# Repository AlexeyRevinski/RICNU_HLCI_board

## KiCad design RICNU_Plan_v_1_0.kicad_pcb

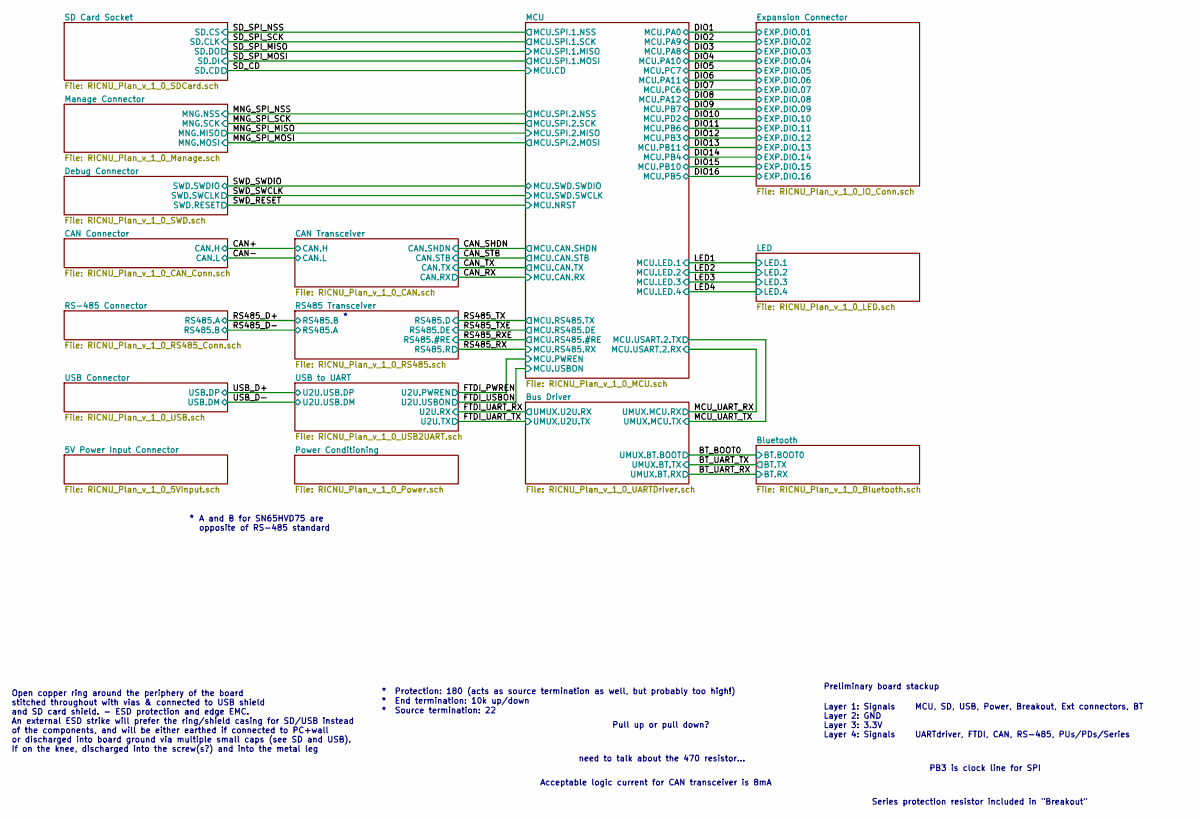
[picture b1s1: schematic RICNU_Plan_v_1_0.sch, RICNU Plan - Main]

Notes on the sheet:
Pull up or pull down?
* Protection: 180 (acts as source termination as well, but probably too high!)
* End termination: 10k up/down
* Source termination: 22
Acceptable logic current for CAN transceiver is 8mA
Series protection resistor included in "Breakout"
need to talk about the 470 resistor...
Open copper ring around the periphery of the board stitched throughout with vias & connected to USB shield and SD card shield. - ESD protection and edge EMC. An external ESD strike will prefer the ring/shield casing for SD/USB instead of the components, and will be either earthed if connected to PC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
PB3 is clock line for SPI
Layer 1: Signals Layer 2: GND Layer 3: 3.3V Layer 4: Signals
MCU, SD, USB, Power, Breakout, Ext connectors, BT UARTdriver, FTDI, CAN, RS-485, PUs/PDs/Series
Preliminary board stackup
A and B for SN65HVD75 are opposite of RS-485 standard

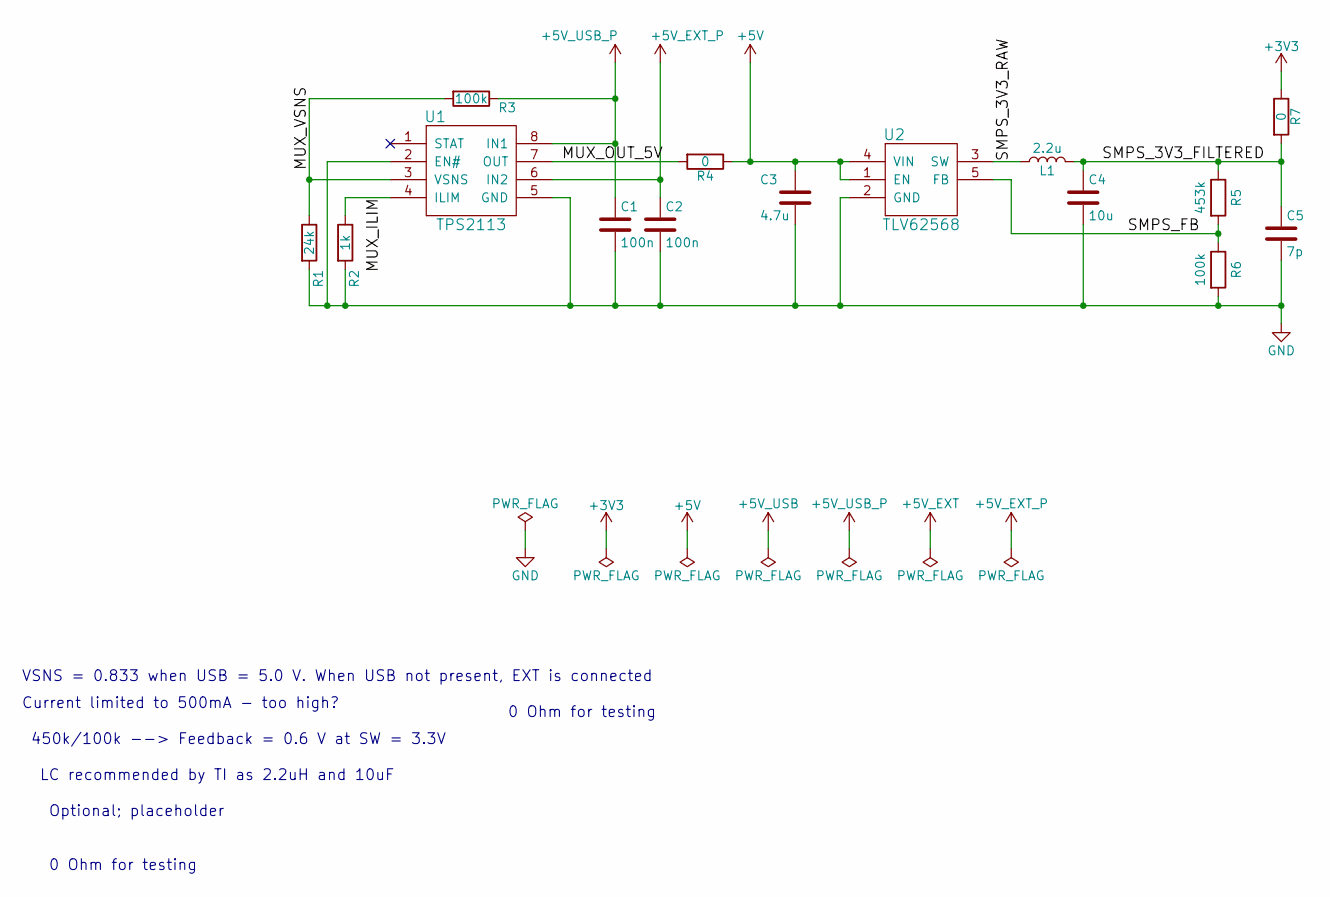
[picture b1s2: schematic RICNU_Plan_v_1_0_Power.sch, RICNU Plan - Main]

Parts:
C1, C2: 100n; C_0402_NoSilk
C3: 4.7u; C_0805
C4: 10u; C_0805
C5: 7p; C_0402_NoSilk
L1: 2.2u; L_Taiyo-Yuden_NR-50xx_HandSoldering
R1: 24k; R_0402_NoSilk
R2: 1k; R_0402_NoSilk
R3, R6: 100k; R_0402_NoSilk
R4, R7: 0; R_0402_NoSilk
R5: 453k; R_0402_NoSilk
U1: TPS2113; TSSOP-8_4.4x3mm_Pitch0.65mm
U2: TLV62568; SOT-23-5

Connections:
+3V3: R7.1; also elsewhere on the board
+5V: C3.1, R4.1, U2.1 (EN), U2.4 (VIN)
+5V_EXT_P: C2.1, U1.6 (IN2); also elsewhere on the board
+5V_USB_P: C1.1, R3.1, U1.8 (IN1); also elsewhere on the board
/Power Conditioning/MUX_ILIM: R2.1, U1.4 (ILIM)
/Power Conditioning/MUX_OUT_5V: R4.2, U1.7 (OUT)
/Power Conditioning/MUX_VSNS: R1.1, R3.2, U1.3 (VSNS)
/Power Conditioning/SMPS_3V3_FILTERED: C4.1, C5.1, L1.2, R5.1, R7.2
/Power Conditioning/SMPS_3V3_RAW: L1.1, U2.3 (SW)
/Power Conditioning/SMPS_FB: R5.2, R6.1, U2.5 (FB)
GND: C1.2, C2.2, C3.2, C4.2, C5.2, R1.2, R2.2, R6.2, U1.2 (EN#), U1.5 (GND), U2.2 (GND); also elsewhere on the board

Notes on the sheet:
0 Ohm for testing
450k/100k --> Feedback = 0.6 V at SW = 3.3V
LC recommended by TI as 2.2uH and 10uF
Optional; placeholder
VSNS = 0.833 when USB = 5.0 V. When USB not present, EXT is connected
Current limited to 500mA - too high?

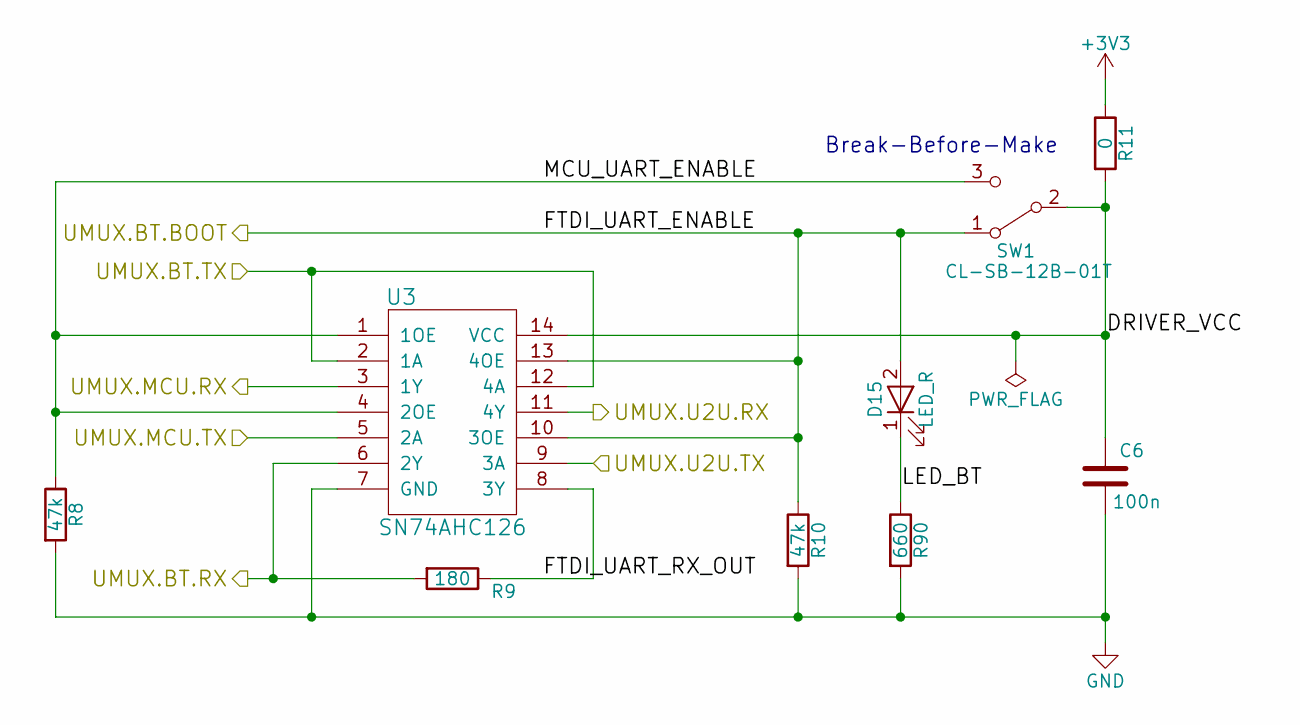
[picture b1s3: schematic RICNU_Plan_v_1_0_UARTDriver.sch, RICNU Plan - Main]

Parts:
C6: 100n; C_0402_NoSilk
D15: LED_R; LED_0402
R8, R10: 47k; R_0402_NoSilk
R9: 180; R_0402_NoSilk
R11: 0; R_0402_NoSilk
R90: 660; R_0402_NoSilk
SW1: CL-SB-12B-01T
U3: SN74AHC126; TSSOP-14_4.4x5mm_Pitch0.65mm

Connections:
+3V3: R11.1; also elsewhere on the board
/BT_BOOT0: D15.2 (A), R10.1, SW1.1 (A), U3.10 (3OE), U3.13 (4OE); also elsewhere on the board
/BT_UART_RX: R9.2, U3.6 (2Y); also elsewhere on the board
/BT_UART_TX: U3.2 (1A), U3.12 (4A); also elsewhere on the board
/Bus Driver/DRIVER_VCC: C6.1, R11.2, SW1.2 (B), U3.14 (VCC)
/Bus Driver/FTDI_UART_RX_OUT: R9.1, U3.8 (3Y)
/Bus Driver/LED_BT: D15.1 (K), R90.1
/Bus Driver/MCU_UART_ENABLE: R8.1, SW1.3 (C), U3.1 (1OE), U3.4 (2OE)
/FTDI_UART_RX: U3.11 (4Y); also elsewhere on the board
/FTDI_UART_TX: U3.9 (3A); also elsewhere on the board
/MCU_UART_RX: U3.3 (1Y); also elsewhere on the board
/MCU_UART_TX: U3.5 (2A); also elsewhere on the board
GND: C6.2, R8.2, R10.2, R90.2, U3.7 (GND); also elsewhere on the board

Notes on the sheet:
Break-Before-Make

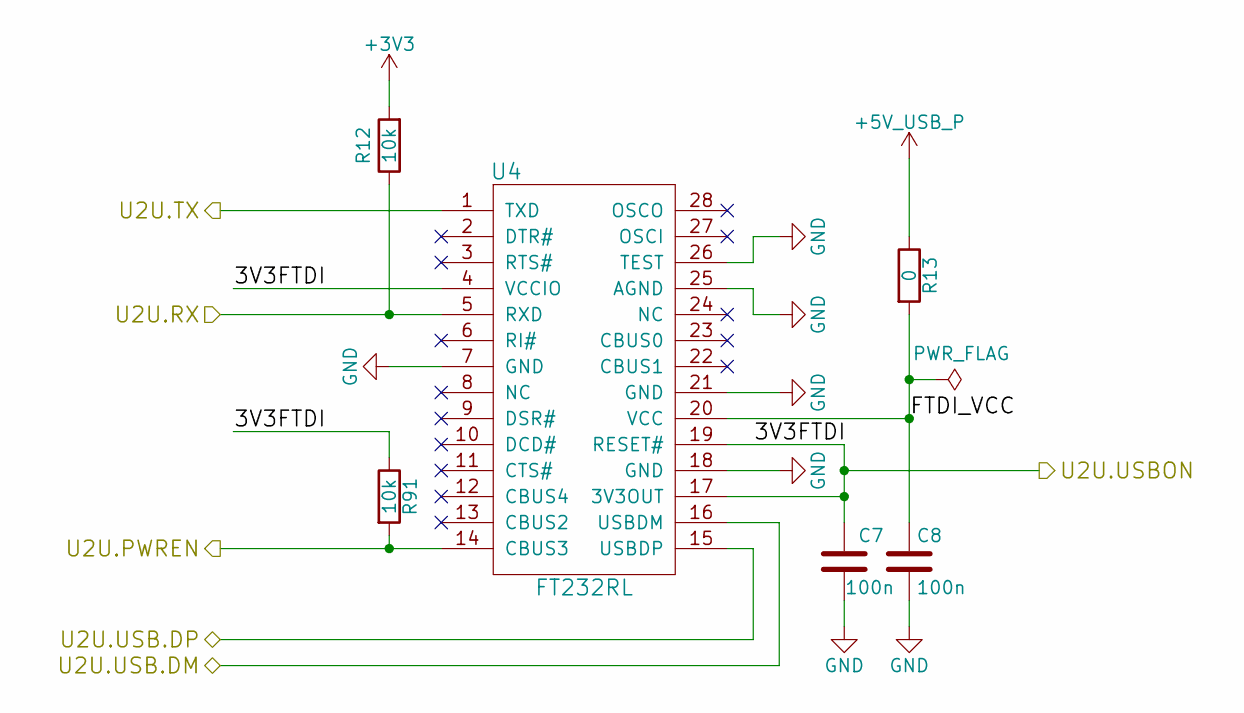
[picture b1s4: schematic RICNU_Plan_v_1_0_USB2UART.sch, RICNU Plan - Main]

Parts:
C7, C8: 100n; C_0402_NoSilk
R12, R91: 10k; R_0402_NoSilk
R13: 0; R_0402_NoSilk
U4: FT232RL; SSOP-28_5.3x10.2mm_Pitch0.65mm

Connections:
+3V3: R12.2; also elsewhere on the board
+5V_USB_P: R13.1; also elsewhere on the board
/FTDI_PWREN: R91.2, U4.14 (CBUS3); also elsewhere on the board
/FTDI_UART_RX: R12.1, U4.5 (RXD); also elsewhere on the board
/FTDI_UART_TX: U4.1 (TXD); also elsewhere on the board
/FTDI_USBON: C7.1, R91.1, U4.4 (VCCIO), U4.17 (3V3OUT), U4.19 (RESET#); also elsewhere on the board
/USB to UART/FTDI_VCC: C8.1, R13.2, U4.20 (VCC)
/USB_D+: U4.15 (USBDP); also elsewhere on the board
/USB_D-: U4.16 (USBDM); also elsewhere on the board
GND: C7.2, C8.2, U4.7 (GND), U4.18 (GND), U4.21 (GND), U4.25 (AGND), U4.26 (TEST); also elsewhere on the board

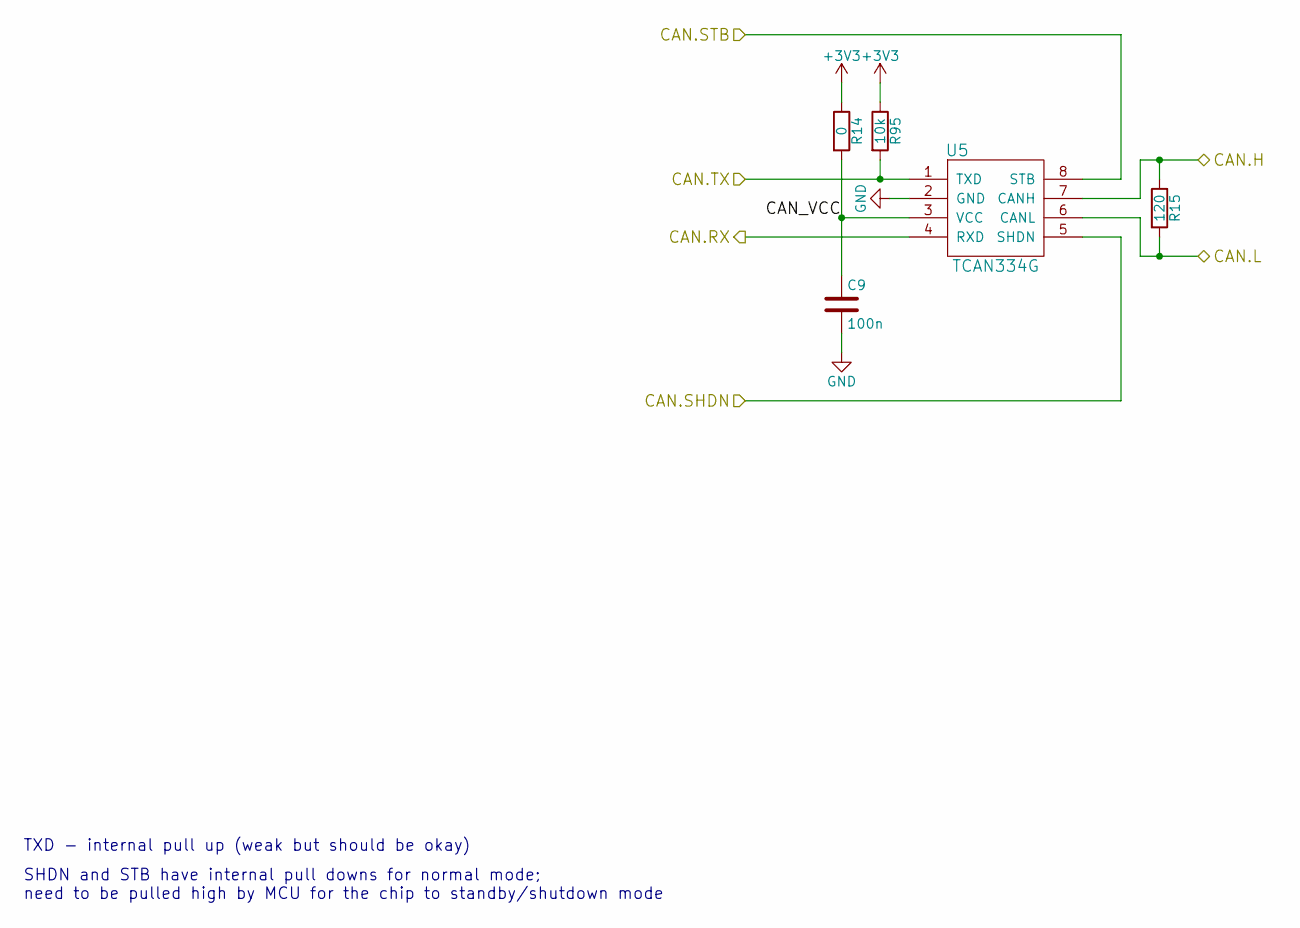
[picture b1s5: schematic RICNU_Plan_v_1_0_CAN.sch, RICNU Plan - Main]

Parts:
C9: 100n; C_0402_NoSilk
R14: 0; R_0402_NoSilk
R15: 120; R_0402_NoSilk
R95: 10k; R_0402_NoSilk
U5: TCAN334G; SOT-23-8

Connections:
+3V3: R14.1, R95.1; also elsewhere on the board
/CAN Transceiver/CAN_VCC: C9.1, R14.2, U5.3 (VCC)
/CAN+: R15.1, U5.7 (CANH); also elsewhere on the board
/CAN-: R15.2, U5.6 (CANL); also elsewhere on the board
/CAN_RX: U5.4 (RXD); also elsewhere on the board
/CAN_SHDN: U5.5 (SHDN); also elsewhere on the board
/CAN_STB: U5.8 (STB); also elsewhere on the board
/CAN_TX: R95.2, U5.1 (TXD); also elsewhere on the board
GND: C9.2, U5.2 (GND); also elsewhere on the board

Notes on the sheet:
SHDN and STB have internal pull downs for normal mode; need to be pulled high by MCU for the chip to standby/shutdown mode
TXD - internal pull up (weak but should be okay)

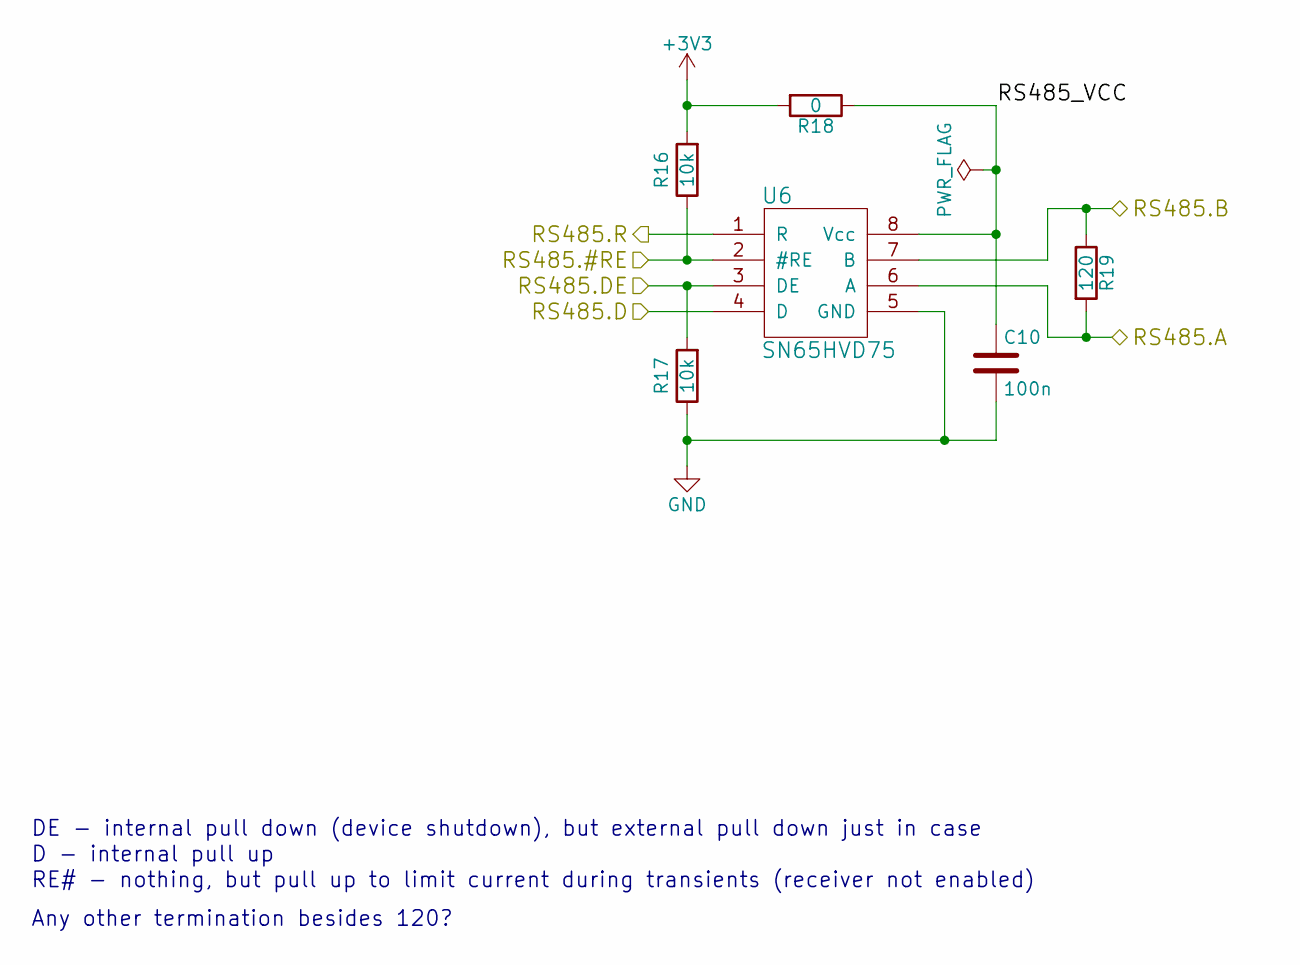
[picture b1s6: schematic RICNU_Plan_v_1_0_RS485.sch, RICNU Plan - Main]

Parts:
C10: 100n; C_0402_NoSilk
R16, R17: 10k; R_0402_NoSilk
R18: 0; R_0402_NoSilk
R19: 120; R_0402_NoSilk
U6: SN65HVD75; VSSOP-8_3.0x3.0mm_Pitch0.65mm

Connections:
+3V3: R16.2, R18.2; also elsewhere on the board
/RS485 Transceiver/RS485_VCC: C10.1, R18.1, U6.8 (Vcc)
/RS485_D+: R19.1, U6.7 (B); also elsewhere on the board
/RS485_D-: R19.2, U6.6 (A); also elsewhere on the board
/RS485_RX: U6.1 (R); also elsewhere on the board
/RS485_RXE: R16.1, U6.2 (#RE); also elsewhere on the board
/RS485_TX: U6.4 (D); also elsewhere on the board
/RS485_TXE: R17.2, U6.3 (DE); also elsewhere on the board
GND: C10.2, R17.1, U6.5 (GND); also elsewhere on the board

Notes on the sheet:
DE - internal pull down (device shutdown), but external pull down just in case
D - internal pull up
RE# - nothing, but pull up to limit current during transients (receiver not enabled)
Any other termination besides 120?

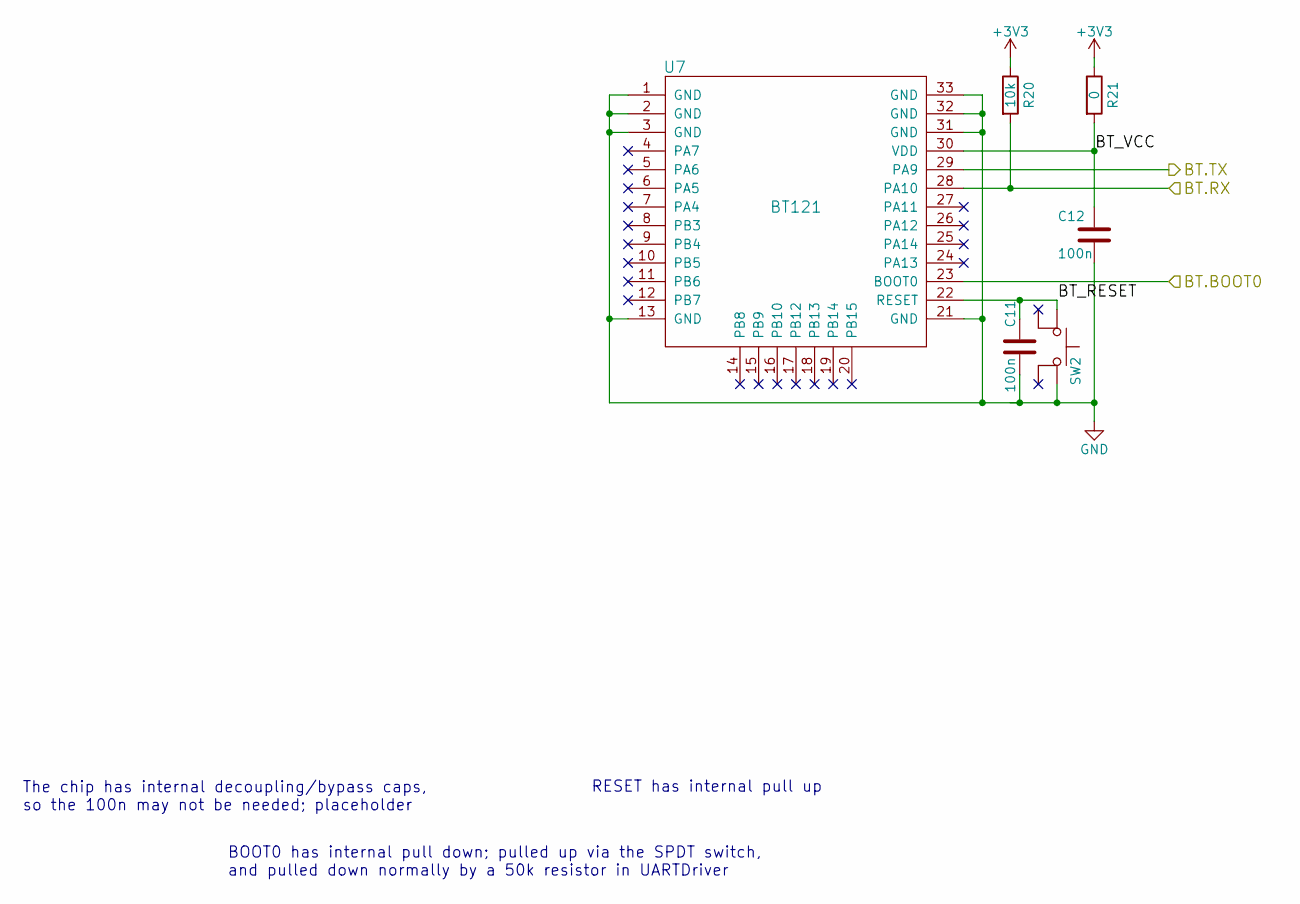
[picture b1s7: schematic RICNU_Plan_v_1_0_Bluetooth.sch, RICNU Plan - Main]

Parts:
C11, C12: 100n; C_0402_NoSilk
R20: 10k; R_0402_NoSilk
R21: 0; R_0402_NoSilk
SW2: SW_Push_4pin; SW_SPST_KMR7
U7: BT121; BT121-A

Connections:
+3V3: R20.1, R21.1; also elsewhere on the board
/BT_BOOT0: U7.23 (BOOT0); also elsewhere on the board
/BT_UART_RX: R20.2, U7.28 (PA10); also elsewhere on the board
/BT_UART_TX: U7.29 (PA9); also elsewhere on the board
/Bluetooth/BT_RESET: C11.1, SW2.1, U7.22 (RESET)
/Bluetooth/BT_VCC: C12.1, R21.2, U7.30 (VDD)
GND: C11.2, C12.2, SW2.2, U7.1 (GND), U7.2 (GND), U7.3 (GND), U7.13 (GND), U7.21 (GND), U7.31 (GND), U7.32 (GND), U7.33 (GND); also elsewhere on the board

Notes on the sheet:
BOOT0 has internal pull down; pulled up via the SPDT switch, and pulled down normally by a 50k resistor in UARTDriver
RESET has internal pull up
The chip has internal decoupling/bypass caps, so the 100n may not be needed; placeholder

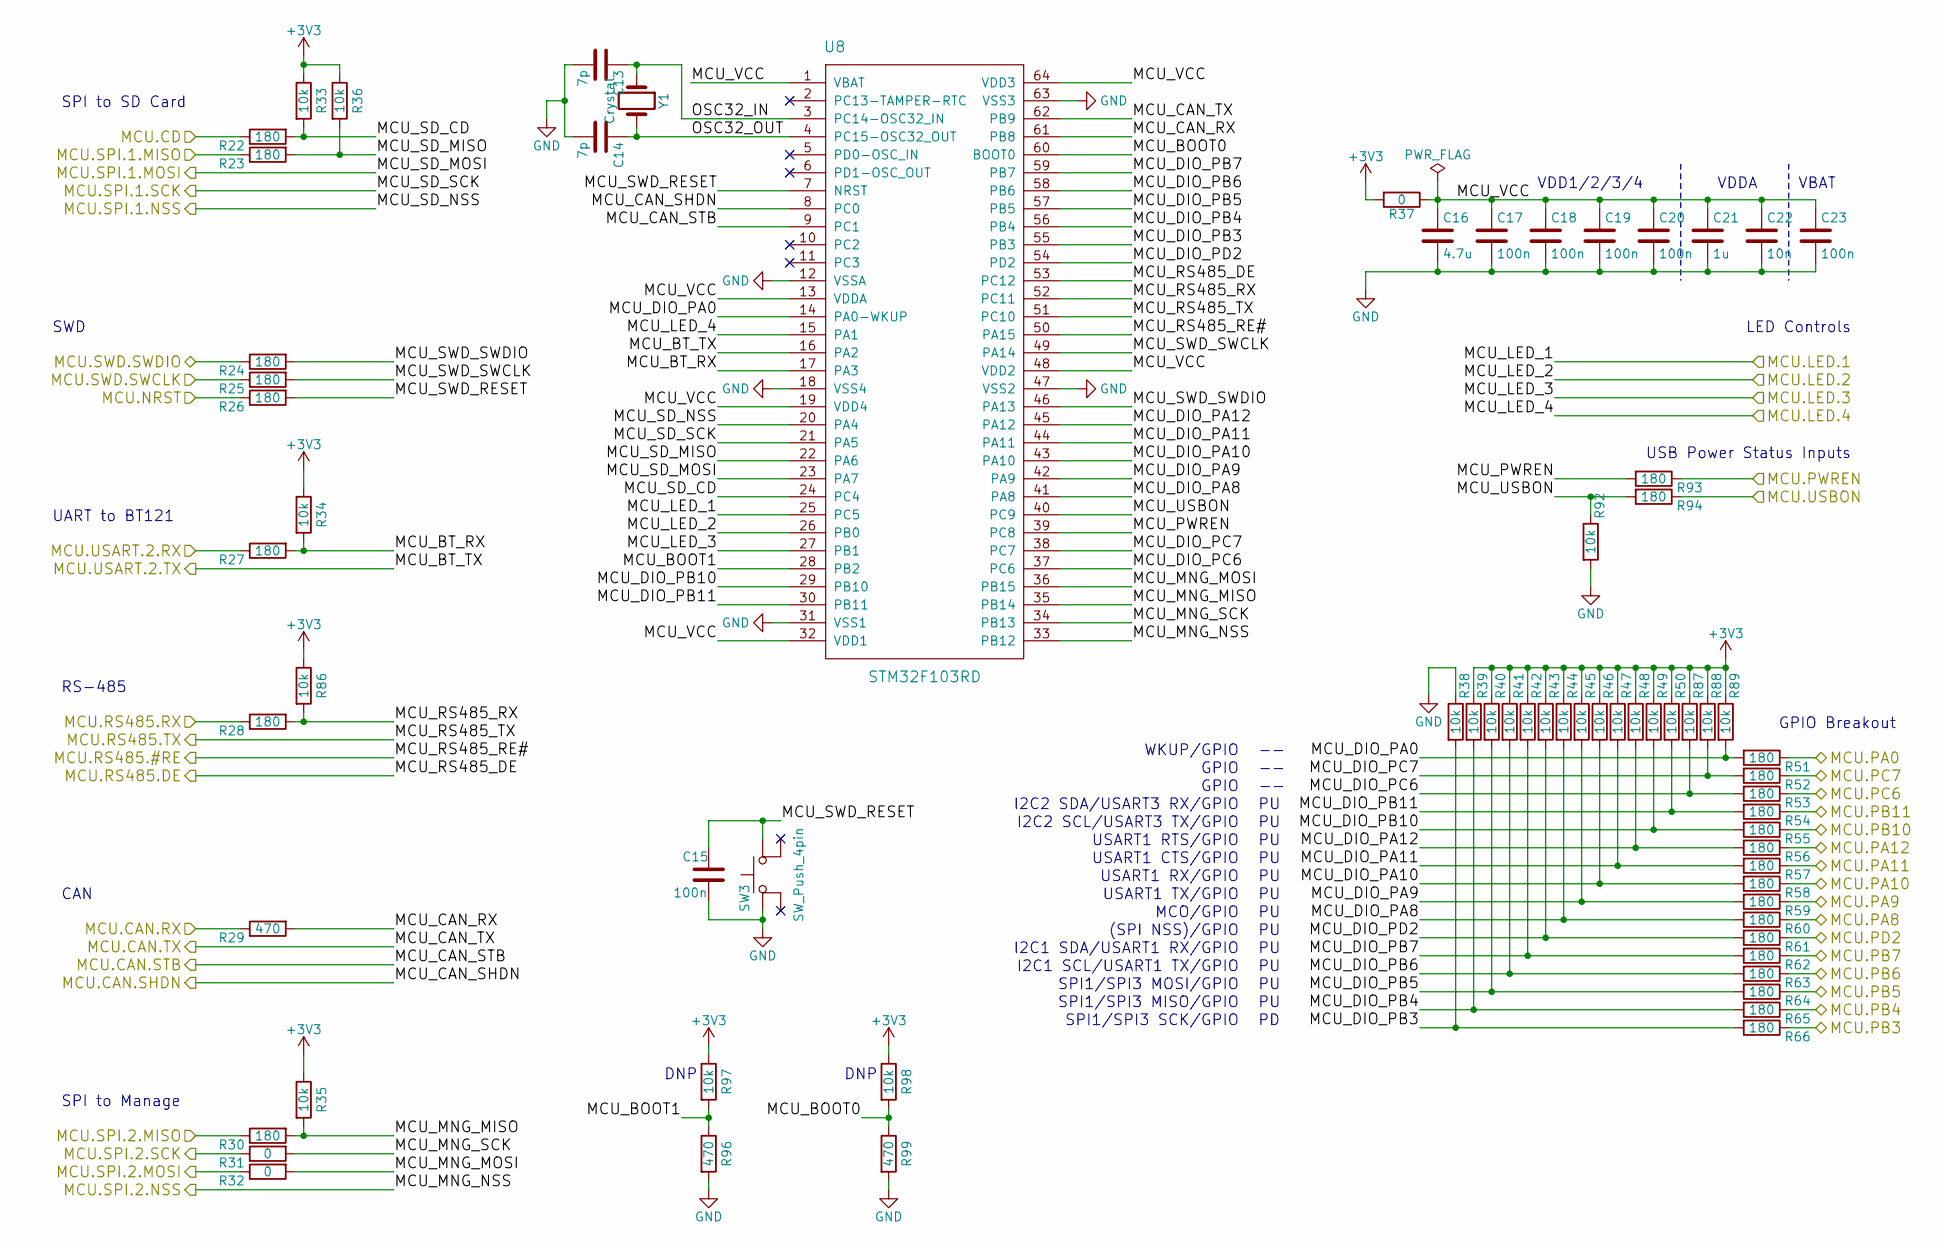
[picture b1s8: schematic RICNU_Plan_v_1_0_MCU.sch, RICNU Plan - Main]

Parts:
C13, C14: 7p; C_0402_NoSilk
C15, C17, C18, C19, C20, C23: 100n; C_0402_NoSilk
C16: 4.7u; C_0805
C21: 1u; C_0805
C22: 10n; C_0402_NoSilk
R22, R23, R24, R25, R26, R27, R28, R30, R51, R52, R53, R54, R55, R56, R57, R58, R59, R60, R61, R62, R63, R64, R65, R66, R93, R94: 180; R_0402_NoSilk
R29, R96, R99: 470; R_0402_NoSilk
R31, R32, R37: 0; R_0402_NoSilk
R33, R34, R35, R36, R38, R39, R40, R41, R42, R43, R44, R45, R46, R47, R48, R49, R50, R86, R87, R88, R89, R92, R97, R98: 10k; R_0402_NoSilk
SW3: SW_Push_4pin; SW_SPST_KMR7
U8: STM32F103RD; TQFP-64_10x10mm_Pitch0.5mm
Y1: Crystal; Crystal_SMD_3215-2pin_3.2x1.5mm

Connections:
+3V3: R33.1, R34.1, R35.1, R36.1, R37.2, R39.1, R40.1, R41.1, R42.1, R43.1, R44.1, R45.1, R46.1, R47.1, R48.1, R49.1, R50.1, R86.1, R87.1, R88.1, R89.1, R97.1, R98.1; also elsewhere on the board
/CAN_RX: R29.1; also elsewhere on the board
/CAN_SHDN: U8.8 (PC0); also elsewhere on the board
/CAN_STB: U8.9 (PC1); also elsewhere on the board
/CAN_TX: U8.62 (PB9); also elsewhere on the board
/DIO1: R51.1; also elsewhere on the board
/DIO2: R59.1; also elsewhere on the board
/DIO3: R60.1; also elsewhere on the board
/DIO4: R58.1; also elsewhere on the board
/DIO5: R52.1; also elsewhere on the board
/DIO6: R57.1; also elsewhere on the board
/DIO7: R53.1; also elsewhere on the board
/DIO8: R56.1; also elsewhere on the board
/DIO9: R62.1; also elsewhere on the board
/DIO10: R61.1; also elsewhere on the board
/DIO11: R63.1; also elsewhere on the board
/DIO12: R66.1; also elsewhere on the board
/DIO13: R54.1; also elsewhere on the board
/DIO14: R65.1; also elsewhere on the board
/DIO15: R55.1; also elsewhere on the board
/DIO16: R64.1; also elsewhere on the board
/FTDI_PWREN: R93.1; also elsewhere on the board
/FTDI_USBON: R94.1; also elsewhere on the board
/LED1: U8.25 (PC5); also elsewhere on the board
/LED2: U8.26 (PB0); also elsewhere on the board
/LED3: U8.27 (PB1); also elsewhere on the board
/LED4: U8.15 (PA1); also elsewhere on the board
/MCU/MCU_BOOT0: R98.2, R99.1, U8.60 (BOOT0)
/MCU/MCU_BOOT1: R96.1, R97.2, U8.28 (PB2)
/MCU/MCU_BT_RX: R27.2, R34.2, U8.17 (PA3)
/MCU/MCU_CAN_RX: R29.2, U8.61 (PB8)
/MCU/MCU_DIO_PA0: R51.2, R89.2, U8.14 (PA0-WKUP)
/MCU/MCU_DIO_PA8: R44.2, R60.2, U8.41 (PA8)
/MCU/MCU_DIO_PA9: R45.2, R59.2, U8.42 (PA9)
/MCU/MCU_DIO_PA10: R46.2, R58.2, U8.43 (PA10)
/MCU/MCU_DIO_PA11: R47.2, R57.2, U8.44 (PA11)
/MCU/MCU_DIO_PA12: R48.2, R56.2, U8.45 (PA12)
/MCU/MCU_DIO_PB3: R38.2, R66.2, U8.55 (PB3)
/MCU/MCU_DIO_PB4: R39.2, R65.2, U8.56 (PB4)
/MCU/MCU_DIO_PB5: R40.2, R64.2, U8.57 (PB5)
/MCU/MCU_DIO_PB6: R41.2, R63.2, U8.58 (PB6)
/MCU/MCU_DIO_PB7: R42.2, R62.2, U8.59 (PB7)
/MCU/MCU_DIO_PB10: R49.2, R55.2, U8.29 (PB10)
/MCU/MCU_DIO_PB11: R50.2, R54.2, U8.30 (PB11)
/MCU/MCU_DIO_PC6: R53.2, R87.2, U8.37 (PC6)
/MCU/MCU_DIO_PC7: R52.2, R88.2, U8.38 (PC7)
/MCU/MCU_DIO_PD2: R43.2, R61.2, U8.54 (PD2)
/MCU/MCU_MNG_MISO: R30.2, R35.2, U8.35 (PB14)
/MCU/MCU_MNG_MOSI: R32.2, U8.36 (PB15)
/MCU/MCU_MNG_SCK: R31.2, U8.34 (PB13)
/MCU/MCU_PWREN: R93.2, U8.39 (PC8)
/MCU/MCU_RS485_RX: R28.2, R86.2, U8.52 (PC11)
/MCU/MCU_SD_CD: R22.2, R33.2, U8.24 (PC4)
/MCU/MCU_SD_MISO: R23.2, R36.2, U8.22 (PA6)
/MCU/MCU_SWD_RESET: C15.1, R26.2, SW3.1, U8.7 (NRST)
/MCU/MCU_SWD_SWCLK: R25.2, U8.49 (PA14)
/MCU/MCU_SWD_SWDIO: R24.2, U8.46 (PA13)
/MCU/MCU_USBON: R92.1, R94.2, U8.40 (PC9)
/MCU/MCU_VCC: C16.1, C17.1, C18.1, C19.1, C20.1, C21.1, C22.1, C23.1, R37.1, U8.1 (VBAT), U8.13 (VDDA), U8.19 (VDD4), U8.32 (VDD1), U8.48 (VDD2), U8.64 (VDD3)
/MCU/OSC32_IN: C13.1, U8.3 (PC14-OSC32_IN), Y1.1
/MCU/OSC32_OUT: C14.1, U8.4 (PC15-OSC32_OUT), Y1.2
/MCU_UART_RX: R27.1; also elsewhere on the board
/MCU_UART_TX: U8.16 (PA2); also elsewhere on the board
/MNG_SPI_MISO: R30.1; also elsewhere on the board
/MNG_SPI_MOSI: R32.1; also elsewhere on the board
/MNG_SPI_NSS: U8.33 (PB12); also elsewhere on the board
/MNG_SPI_SCK: R31.1; also elsewhere on the board
/RS485_RX: R28.1; also elsewhere on the board
/RS485_RXE: U8.50 (PA15); also elsewhere on the board
/RS485_TX: U8.51 (PC10); also elsewhere on the board
/RS485_TXE: U8.53 (PC12); also elsewhere on the board
/SD_CD: R22.1; also elsewhere on the board
/SD_SPI_MISO: R23.1; also elsewhere on the board
/SD_SPI_MOSI: U8.23 (PA7); also elsewhere on the board
/SD_SPI_NSS: U8.20 (PA4); also elsewhere on the board
/SD_SPI_SCK: U8.21 (PA5); also elsewhere on the board
/SWD_RESET: R26.1; also elsewhere on the board
/SWD_SWCLK: R25.1; also elsewhere on the board
/SWD_SWDIO: R24.1; also elsewhere on the board
GND: C13.2, C14.2, C15.2, C16.2, C17.2, C18.2, C19.2, C20.2, C21.2, C22.2, C23.2, R38.1, R92.2, R96.2, R99.2, SW3.2, U8.12 (VSSA), U8.18 (VSS4), U8.31 (VSS1), U8.47 (VSS2), U8.63 (VSS3); also elsewhere on the board

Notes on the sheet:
VBAT
VDDA
VDD1/2/3/4
CAN
SPI to Manage
RS-485
UART to BT121
SWD
SPI to SD Card
SPI1/SPI3 SCK/GPIO
SPI1/SPI3 MISO/GPIO
SPI1/SPI3 MOSI/GPIO
I2C1 SCL/USART1 TX/GPIO
I2C1 SDA/USART1 RX/GPIO
(SPI NSS)/GPIO
MCO/GPIO
USART1 TX/GPIO
USART1 RX/GPIO
USART1 CTS/GPIO
USART1 RTS/GPIO
I2C2 SCL/USART3 TX/GPIO
I2C2 SDA/USART3 RX/GPIO
GPIO
WKUP/GPIO
GPIO Breakout
LED Controls
USB Power Status Inputs
DNP

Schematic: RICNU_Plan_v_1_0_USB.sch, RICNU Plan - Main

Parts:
C24, C25, C26: 47p; C_0402_NoSilk
C27: 10n; C_0402_NoSilk
C28: 100n; C_0402_NoSilk
C29: 4.7u; C_0805
D1: 5.0V TVS; D_SOD-523
D2: 5.6V; D_SMA_Handsoldering
F1: PTC 200mA; R_0603_HandSoldering
FB1: Ferrite Bead; R_0402_NoSilk
J1: USB_OTG; USB_Micro-B_Molex-105017-0001
Q1: N-CH; SOT-23
R67: 4.7k; R_0402_NoSilk
R68: 0; R_0402_NoSilk
TVS1: TPD2EUSB30A; Texas_DRT-3

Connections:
+5V_USB: F1.2, J1.1 (VBUS)
+5V_USB_P: R68.1; also elsewhere on the board
/USB Connector/GND_USB_CABLE: C24.1, C25.1, C26.1, D1.2 (A2), J1.5 (GND), Q1.3 (D), R67.2, TVS1.3 (GND)
/USB Connector/USB_SHIELD: C24.2, J1.6 (Shield), R67.1
/USB Connector/VBUS_PROTECTED: C27.1, D1.1 (A1), D2.1 (K), F1.1, FB1.2, Q1.1 (G)
/USB Connector/VBUS_PROTECTED_FILTERED: C28.1, C29.1, FB1.1, R68.2
/USB_D+: C25.2, J1.3 (D+), TVS1.1 (D+); also elsewhere on the board
/USB_D-: C26.2, J1.2 (D-), TVS1.2 (D-); also elsewhere on the board
GND: C27.2, C28.2, C29.2, D2.2 (A), Q1.2 (S); also elsewhere on the board

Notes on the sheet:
* A strike on the shield will go through the 47p cap; 4.7k to stop that energy from bouncing back (recommendation, unclear)
* Ferrite bead suppresses any EMI from upstream or downstream
* Add a common mode choke on data lines? Differential + twisted pair
* Zener should clamp at 5.6V but fuse is the only current limiter here... Should trip at 500mA (max through Zener is 534 mA) but TIME!!!
* TVS on the power line will discharge ESD into cable ground
* MOSFET - normally shorts out the internal diode; if reverse plug, won't connect drain and source; device is disconnected from cable ground
* 10n/bead/100n/4.7u - recommendation from FTDI on filtering... not sure why bead is after 10n
* Fuse - after tripping, 2.3Ohms max. Average expected current - 50-70 mA; Dissipated P = R*I^2 = 6 to 11 mW
NPO/C0G

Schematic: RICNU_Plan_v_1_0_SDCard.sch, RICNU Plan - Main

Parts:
C30, C31: 100n; C_0402_NoSilk
C32: 4.7u; C_0805
C33: 47p; C_0402_NoSilk
D3, D14: 3.3V TVS; D_SOD-523
F2: PTC 200 mA; R_0603_HandSoldering
R69, R70, R71: 10k; R_0402_NoSilk
R72: 0; R_0402_NoSilk
R73: 4.7k; R_0402_NoSilk
SD1: DM3AT-SF-PEJM5; Hirose_DM3AT-SF-PEJM5
TVS2: TPD4E004; Fairchild_MicroPak-6_1.0x1.45mm_Pitch0.5mm

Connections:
+3V3: C30.1, R69.1, R71.1, R72.2, TVS2.6 (VCC); also elsewhere on the board
/SD Card Socket/SD_SHIELD: C33.2, R73.2, SD1.11 (SHIELD)
/SD Card Socket/SD_VDD: F2.2, SD1.4 (VDD)
/SD Card Socket/SD_VDD_P: C31.1, C32.1, D3.1 (A1), F2.1, R72.1
/SD_CD: D14.1 (A1), SD1.9 (CDB); also elsewhere on the board
/SD_SPI_MISO: SD1.7 (DAT0/DO), TVS2.4 (IO3); also elsewhere on the board
/SD_SPI_MOSI: R71.2, SD1.3 (CMD/DI), TVS2.1 (IO1); also elsewhere on the board
/SD_SPI_NSS: R69.2, SD1.2 (DAT3/CS), TVS2.2 (IO2); also elsewhere on the board
/SD_SPI_SCK: R70.1, SD1.5 (CLK), TVS2.5 (IO4); also elsewhere on the board
GND: C30.2, C31.2, C32.2, C33.1, D3.2 (A2), D14.2 (A2), R70.2, R73.1, SD1.6 (VSS), SD1.10 (CDA), TVS2.3 (GND); also elsewhere on the board

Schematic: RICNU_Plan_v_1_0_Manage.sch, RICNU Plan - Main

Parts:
C34: 100n; C_0402_NoSilk
D4: D_Schottky; D_SOD-323
D5: 3.3V TVS; D_SOD-523
J2: MOLEX-PC6; Molex_PicoClasp_501568-0607_1x06_P1.0mm_RightAngle
R74, R75, R76: 10k; R_0402_NoSilk
R77: 180; R_0402_NoSilk
TVS3: TPD4E004; Fairchild_MicroPak-6_1.0x1.45mm_Pitch0.5mm

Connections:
+3V3: C34.1, R74.1, R76.1, R77.2, TVS3.6 (VCC); also elsewhere on the board
/MNG_SPI_MISO: J2.4, TVS3.4 (IO3); also elsewhere on the board
/MNG_SPI_MOSI: J2.5, R76.2, TVS3.5 (IO4); also elsewhere on the board
/MNG_SPI_NSS: J2.2, R74.2, TVS3.1 (IO1); also elsewhere on the board
/MNG_SPI_SCK: J2.3, R75.1, TVS3.2 (IO2); also elsewhere on the board
/Manage Connector/MNG_SCHKY: D4.2 (A), R77.1
/Manage Connector/MNG_VREF: D4.1 (K), D5.1 (A1), J2.1
GND: C34.2, D5.2 (A2), J2.6, R75.2, TVS3.3 (GND); also elsewhere on the board

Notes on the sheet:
CPDQC3V3T-HF
TBX0104 on MNG side
VREF
NSS
SCK
MISO
MOSI
GND

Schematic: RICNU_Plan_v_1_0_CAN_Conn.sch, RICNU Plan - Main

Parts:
J3: DF52-4S-0.8H(21); Hirose_DF52-4S-0.8H_04x0.80mm_Angled
TVS4: CDSOT23-T24CAN; SOT-23

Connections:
/CAN+: J3.3, TVS4.1 (IO1); also elsewhere on the board
/CAN-: J3.4, TVS4.2 (IO2); also elsewhere on the board
GND: J3.2, TVS4.3 (GND); also elsewhere on the board

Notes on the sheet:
VIN
CANH
CANL
GND

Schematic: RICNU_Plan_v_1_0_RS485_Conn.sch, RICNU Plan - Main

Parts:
J4: DF52-4S-0.8H(21); Hirose_DF52-4S-0.8H_04x0.80mm_Angled
TVS5: CDSOT23-SM712; SOT-23

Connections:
/RS485_D+: J4.3, TVS5.1 (IO1); also elsewhere on the board
/RS485_D-: J4.4, TVS5.2 (IO2); also elsewhere on the board
GND: J4.2, TVS5.3 (GND); also elsewhere on the board

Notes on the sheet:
GND
DB+
DA-

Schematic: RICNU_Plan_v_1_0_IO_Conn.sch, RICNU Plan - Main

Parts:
J5: MOLEX-PC20; Molex_PicoClasp_501571-2007_2x10_P1.0mm_RightAngle
TVS6, TVS7, TVS8, TVS9: TPD4E004; Fairchild_MicroPak-6_1.0x1.45mm_Pitch0.5mm

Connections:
+3V3: TVS6.6 (VCC), TVS7.6 (VCC), TVS8.6 (VCC), TVS9.6 (VCC); also elsewhere on the board
/DIO1: J5.1, TVS6.5 (IO4); also elsewhere on the board
/DIO2: J5.20, TVS6.1 (IO1); also elsewhere on the board
/DIO3: J5.2, TVS6.4 (IO3); also elsewhere on the board
/DIO4: J5.19, TVS6.2 (IO2); also elsewhere on the board
/DIO5: J5.3, TVS7.5 (IO4); also elsewhere on the board
/DIO6: J5.18, TVS7.1 (IO1); also elsewhere on the board
/DIO7: J5.4, TVS7.4 (IO3); also elsewhere on the board
/DIO8: J5.17, TVS7.2 (IO2); also elsewhere on the board
/DIO9: J5.7, TVS8.5 (IO4); also elsewhere on the board
/DIO10: J5.14, TVS8.1 (IO1); also elsewhere on the board
/DIO11: J5.8, TVS8.4 (IO3); also elsewhere on the board
/DIO12: J5.13, TVS8.2 (IO2); also elsewhere on the board
/DIO13: J5.9, TVS9.5 (IO4); also elsewhere on the board
/DIO14: J5.12, TVS9.1 (IO1); also elsewhere on the board
/DIO15: J5.10, TVS9.4 (IO3); also elsewhere on the board
/DIO16: J5.11, TVS9.2 (IO2); also elsewhere on the board
GND: J5.5, J5.6, J5.15, J5.16, TVS6.3 (GND), TVS7.3 (GND), TVS8.3 (GND), TVS9.3 (GND); also elsewhere on the board

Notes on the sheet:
180R limits current to 22.78 mA max if two sides disagree on output level and external voltage is higher or lower than supply
Diodes clamp between -0.8 to 4.1V
Also limit injection current to 2.78 mA if signals go below 0 and above 3.3. ESD clamps at -0.8 and 4.1V. All pins except for SPI NSS are 5V tolerant. So, -0.3 - -0.8 = -0.5; -0.5/180 = -2.78mA
All pins except for SPI NSS are 5V tolerant, too

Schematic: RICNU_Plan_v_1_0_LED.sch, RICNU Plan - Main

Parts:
D6: LED_R; LED_0402
D7: LED_Y; LED_0402
D8: LED_G; LED_0402
D9: LED_B; LED_0402
R78: 620; R_0402_NoSilk
R79, R80: 470; R_0402_NoSilk
R81: 180; R_0402_NoSilk

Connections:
+3V3: R78.1, R79.1, R80.1, R81.1; also elsewhere on the board
/LED1: D6.1 (K); also elsewhere on the board
/LED2: D7.1 (K); also elsewhere on the board
/LED3: D8.1 (K); also elsewhere on the board
/LED4: D9.1 (K); also elsewhere on the board
/LED/LED1_R: D6.2 (A), R78.2
/LED/LED2_R: D7.2 (A), R79.2
/LED/LED3_R: D8.2 (A), R80.2
/LED/LED4_R: D9.2 (A), R81.2

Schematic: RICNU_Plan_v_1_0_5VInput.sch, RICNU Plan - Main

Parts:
C35: 4.7u; C_0805
C36: 100n; C_0402_NoSilk
D10: 5.6V; D_SMA_Handsoldering
D11: 5.0V TVS; D_SOD-523
F3: PTC 200mA; R_0603_HandSoldering
J6: 2x0.1; Pin_Header_Straight_1x02_Pitch2.54mm
Q2: N-CH; SOT-23
R82: 0; R_0402_NoSilk

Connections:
+5V_EXT: F3.1, J6.1
+5V_EXT_P: R82.2; also elsewhere on the board
/5V Power Input Connector/5V_INP_PROTECTED: C35.1, C36.1, D10.1 (K), D11.1 (A1), F3.2, Q2.1 (G), R82.1
/5V Power Input Connector/GND_5V_INPUT: D11.2 (A2), J6.2, Q2.3 (D)
GND: C35.2, C36.2, D10.2 (A), Q2.2 (S); also elsewhere on the board

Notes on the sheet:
VIN
GND

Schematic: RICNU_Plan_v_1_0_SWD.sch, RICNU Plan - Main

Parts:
C37: 100n; C_0402_NoSilk
D12: 3.3V TVS; D_SOD-523
D13: D_Schottky; D_SOD-323
J7: FH19C-6S-0.5SH(05)
R83, R84: 10k; R_0402_NoSilk
R85: 180; R_0402_NoSilk
TVS10: TPD4E004; Fairchild_MicroPak-6_1.0x1.45mm_Pitch0.5mm

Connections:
+3V3: C37.2, R83.1, R85.2, TVS10.6 (VCC); also elsewhere on the board
/Debug Connector/SWD_SCHKY: D13.2 (A), R85.1
/Debug Connector/SWD_VREF: D12.1 (A1), D13.1 (K), J7.6
/SWD_RESET: J7.3, TVS10.1 (IO1); also elsewhere on the board
/SWD_SWCLK: J7.4, R84.1, TVS10.2 (IO2); also elsewhere on the board
/SWD_SWDIO: J7.5, R83.2, TVS10.4 (IO3); also elsewhere on the board
GND: C37.1, D12.2 (A2), J7.2, R84.2, TVS10.3 (GND); also elsewhere on the board

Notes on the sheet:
* Reverse plug not likely... Perhaps internal short in the debugger can happen - that's why there is a fuse
* In case of reverse plug, Vref ends up on Reset - still 3.3V, but data lines are grounded
* Zener not necessary? I am supplying the 3V3 to the debugger for level translation; overvoltage not likely
VREF
SWDIO
SWCLK
RESET
GND
SWO
